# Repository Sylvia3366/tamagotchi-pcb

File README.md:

# tamagotchi-pcb
Finally, edit your README to include the submission requirements:

A short description of what your project is
A couple sentences on why you made the project
A couple sentences on how to use your project
Pictures of your project:

A screenshot of a full 3D model of your project
A screenshot of your PCB, if you have one
A wiring diagram, if you're doing any wiring that isn't on a PCB
A BOM (Bill of Materials) in table format at the end of the README, with links.

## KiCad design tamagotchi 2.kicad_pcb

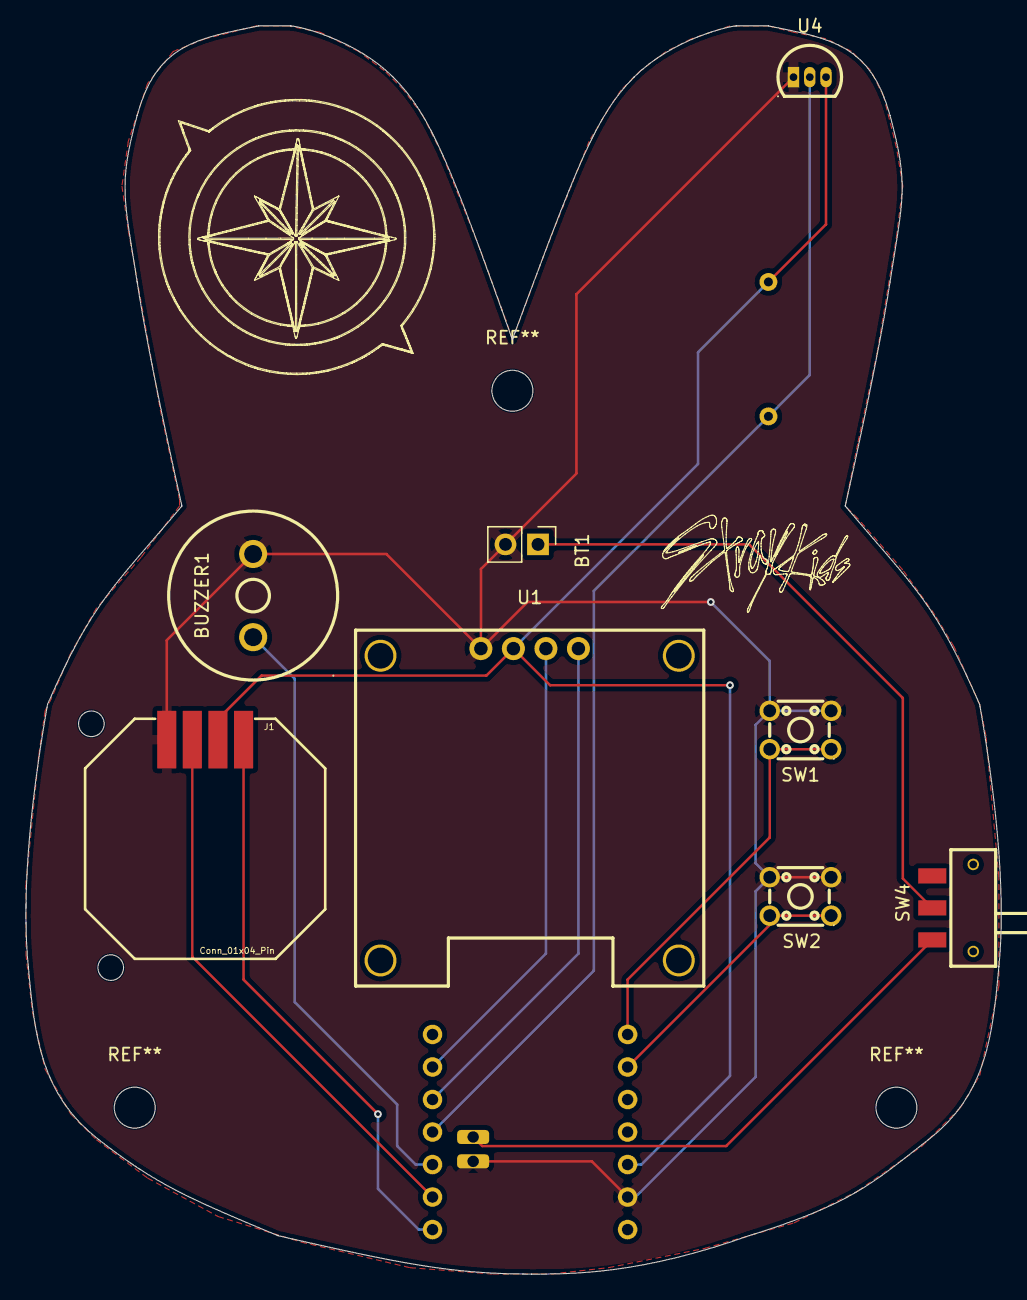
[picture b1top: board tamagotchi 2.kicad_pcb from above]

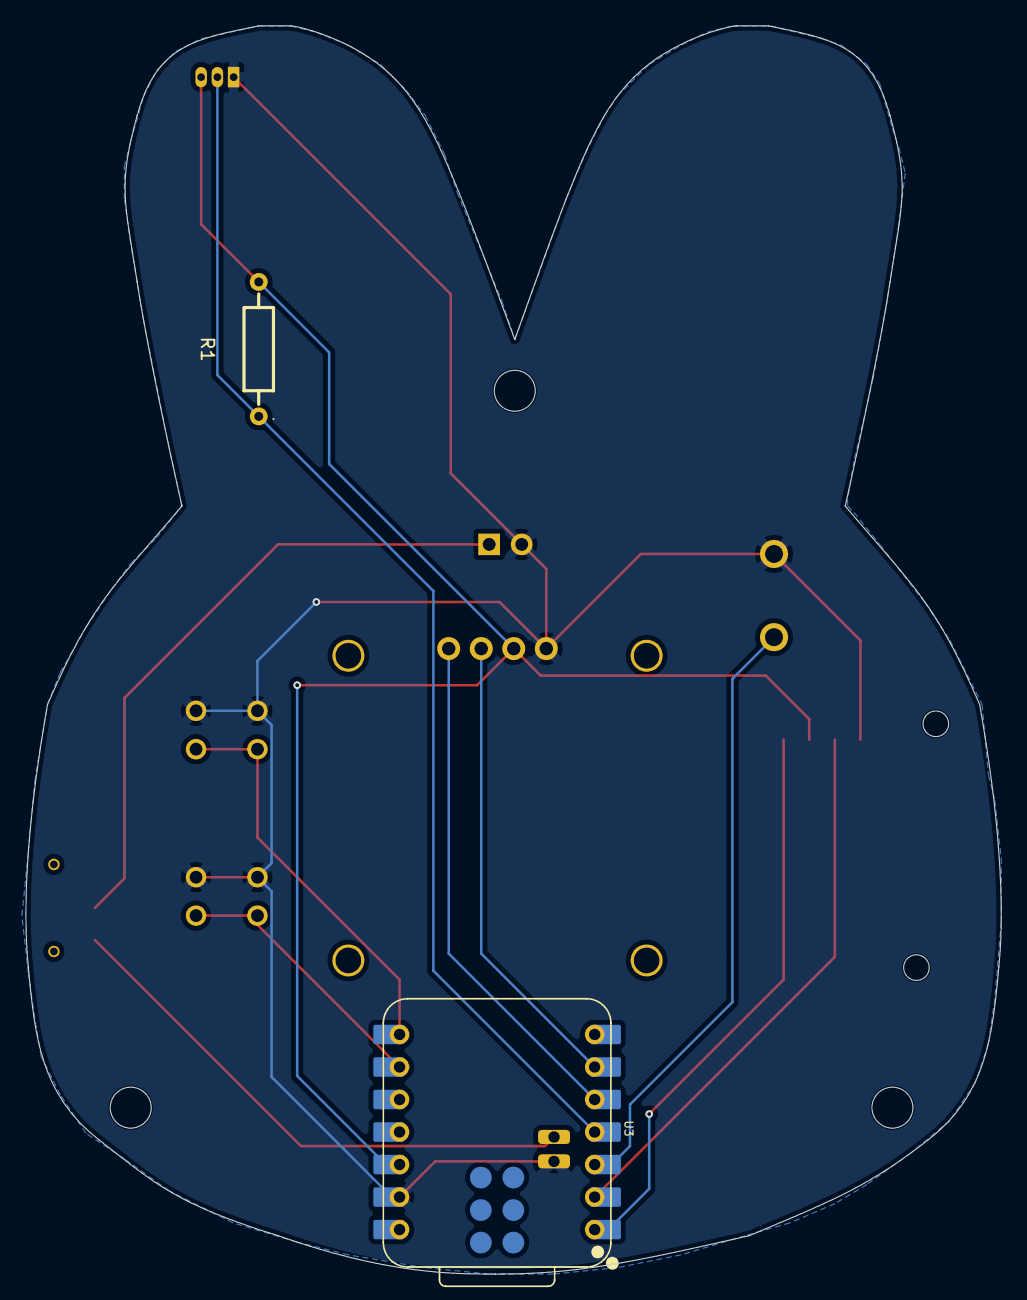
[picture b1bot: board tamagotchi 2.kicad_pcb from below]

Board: 2 copper layers, 76.2 x 97.5 mm, 10 parts (2 on the bottom side), 12 nets.

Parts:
BT1: Battery_Cell; PinHeader_1x02_P2.54mm_Vertical
BUZZER1: 1207-P6.5MM; BUZ-TH_BD12.5-P6.50-D1.4
J1: Conn_01x04_Pin; JOYSTICK-PSP1000
R1: 4.7k; RES-TH_BD2.3-L6.5-P10.50-D0.5
SW1, SW2: SW_Push; SW-TH_4P-L4.5-W4.5-P3.00-LS4.8
SW4: MST-12D18G4 SPDT SLIDE SWITCH; SW-SMD_MST-12D18G4-SPDT-SLIDE-SWITCH
U1: HS96L03W2C03; OLED-TH_L27.8-W27.2-P2.54_C9900033791
U3: XIAO-ESP32-C3-SMD; XIAO-ESP32-C3-DIP-SMD
U4: DS18B20; TO-92-3_L4.9-W3.7-P1.27-L

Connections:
+3V3: J1.2, R1.2, U1.2 (VCC), U3.12 (3V3), U4.3 (V_{DD})
+BATT: SW4.1, U3.15 (BAT)
GND: BT1.2 (-), BUZZER1.2 (-), J1.4, SW1.1 (2_2), SW2.1 (2_2), U1.1 (GND), U3.13 (GND), U3.16 (GND), U4.1 (GND)
unnamed: BT1.1 (+), SW4.2
unnamed: BUZZER1.1 (+), U3.3 (GPIO4_A2_D2)
unnamed: J1.1, U3.1 (GPIO2_A0_D0)
unnamed: J1.3, U3.2 (GPIO3_A1_D1)
unnamed: U1.3 (SCL), U3.6 (GPIO7_D5_SCL)
unnamed: U1.4 (SDA), U3.5 (GPIO6_D4_SDA)
unnamed: R1.1, U3.4 (GPIO5_A3_D3), U4.2 (DQ)
unnamed: SW2.2 (1_1), U3.9 (GPIO8_D8_SCK)
unnamed: SW1.2 (1_1), U3.8 (GPIO20_D7_RX)

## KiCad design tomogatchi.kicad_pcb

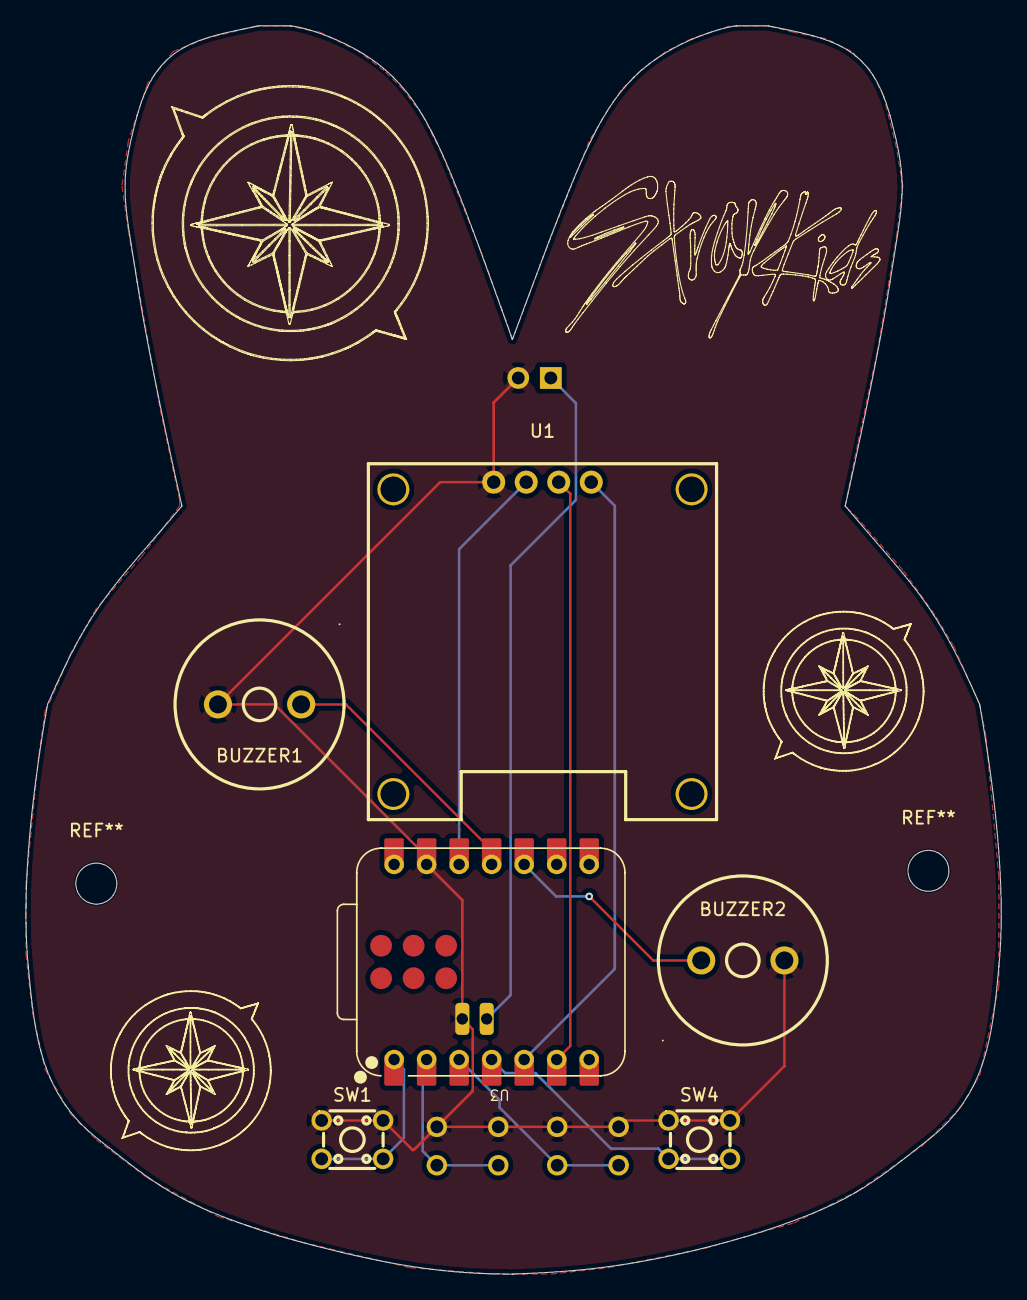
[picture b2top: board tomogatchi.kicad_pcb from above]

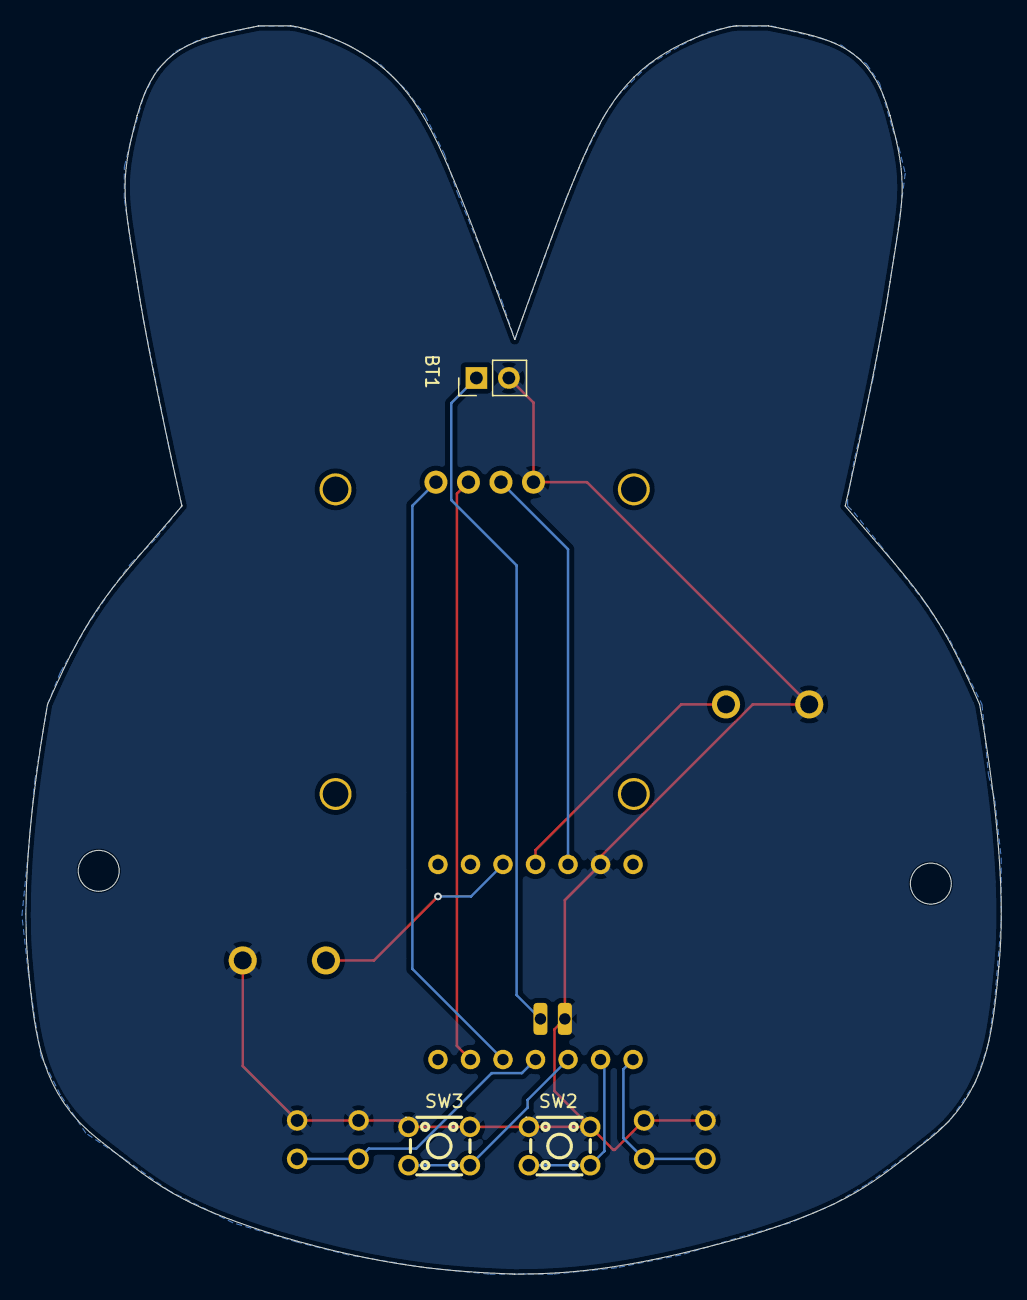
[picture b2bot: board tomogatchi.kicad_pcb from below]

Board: 2 copper layers, 76.2 x 97.5 mm, 9 parts (3 on the bottom side), 11 nets.

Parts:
BT1: Battery_Cell; PinHeader_1x02_P2.54mm_Vertical
BUZZER1, BUZZER2: 1207-P6.5MM; BUZ-TH_BD12.5-P6.50-D1.4
SW1, SW2, SW3, SW4: SW_Push; SW-TH_4P-L4.5-W4.5-P3.00-LS4.8
U1: HS96L03W2C03; OLED-TH_L27.8-W27.2-P2.54_C9900033791
U3: XIAO-ESP32-C3-SMD; XIAO-ESP32-C3-DIP-SMD

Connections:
+3V3: U1.2 (VCC), U3.12 (3V3)
+BATT: BT1.1 (+), U3.15 (BAT)
GND: BT1.2 (-), BUZZER1.2 (-), BUZZER2.2 (-), SW1.1, SW2.1, SW3.1, SW4.1, U1.1 (GND), U3.13 (GND), U3.16 (GND)
unnamed: BUZZER1.1 (+), U3.11 (GPIO10_D10_MOSI)
unnamed: BUZZER2.1 (+), U3.10 (GPIO9_D9_MISO)
unnamed: U1.3 (SCL), U3.6 (GPIO7_D5_SCL)
unnamed: U1.4 (SDA), U3.5 (GPIO6_D4_SDA)
unnamed: SW1.2, U3.1 (GPIO2_A0_D0)
unnamed: SW2.2, U3.2 (GPIO3_A1_D1)
unnamed: SW3.2, U3.3 (GPIO4_A2_D2)
unnamed: SW4.2, U3.4 (GPIO5_A3_D3)
